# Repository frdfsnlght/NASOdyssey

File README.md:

# NASOdyssey
3D printed NAS based on the Odyssey X86J4125864

[Documentaion](https://frdfsnlght.github.io/NASOdyssey/)

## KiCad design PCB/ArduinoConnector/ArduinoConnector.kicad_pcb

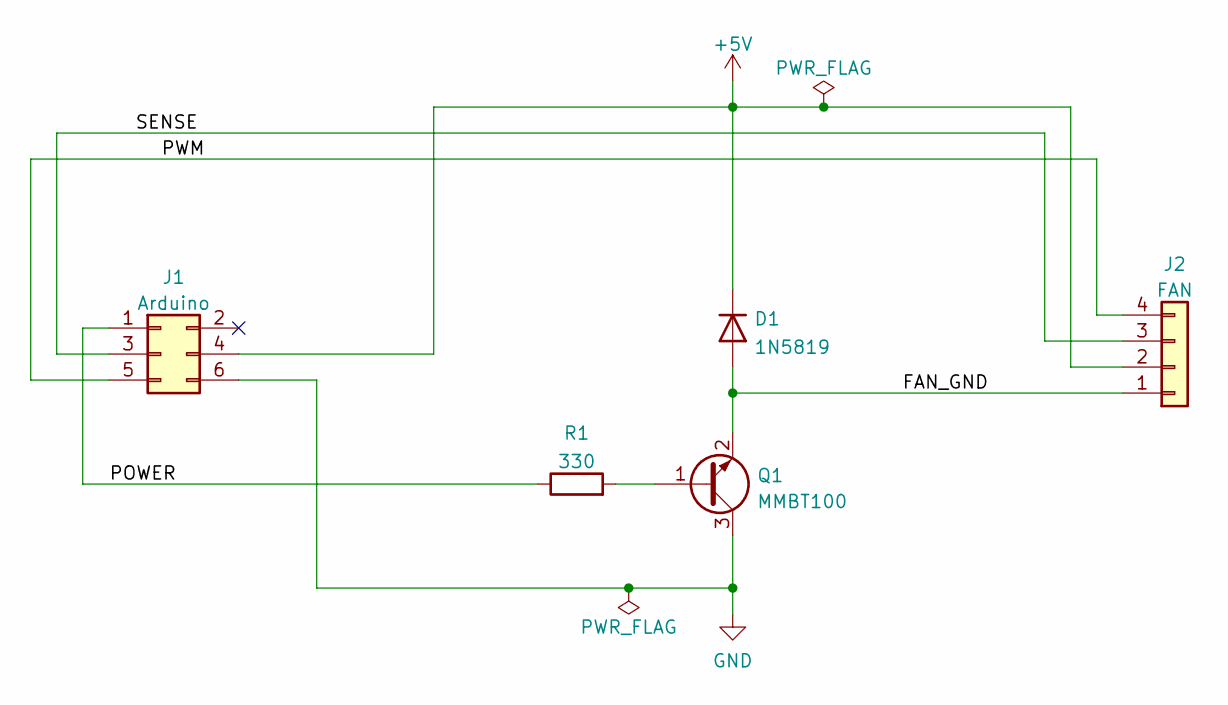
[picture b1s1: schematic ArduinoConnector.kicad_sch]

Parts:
D1: 1N5819; D_SMA
J1: Arduino; PinHeader_2x03_P2.54mm_Vertical
J2: FAN; Molex_KK-254_AE-6410-04A_1x04_P2.54mm_Vertical
Q1: MMBT100; SOT-23
R1: 330; R_0805_2012Metric

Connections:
+5V: D1.1 (K), J1.4, J2.2
/FAN_GND: D1.2 (A), J2.1, Q1.2 (E)
/POWER: J1.1, R1.1
/PWM: J1.5, J2.4
/SENSE: J1.3, J2.3
GND: J1.6, Q1.3 (C)
unnamed: Q1.1 (B), R1.2

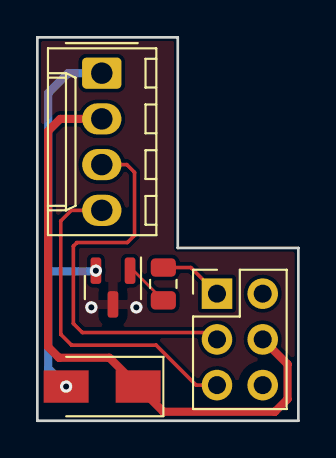
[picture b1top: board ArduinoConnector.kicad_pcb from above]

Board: 2 copper layers, 14.5 x 21.3 mm, 5 parts (0 on the bottom side), 7 nets.

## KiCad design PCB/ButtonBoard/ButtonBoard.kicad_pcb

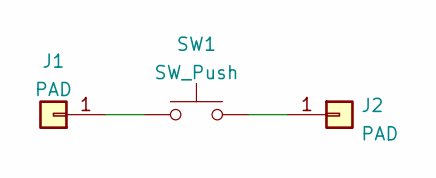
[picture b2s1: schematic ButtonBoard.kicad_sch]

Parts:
J1, J2: PAD; Pin_D1.3mm_L11.0mm
SW1: SW_Push; SW_Push_1P1T_NO_6x6mm_H9.5mm

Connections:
unnamed: J1.1, SW1.1
unnamed: J2.1, SW1.2

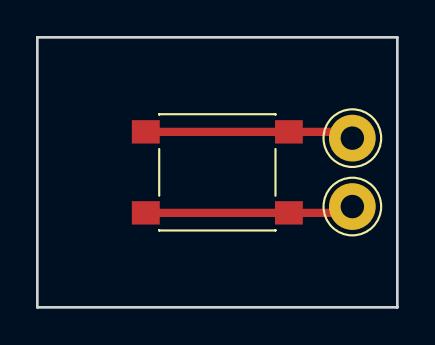
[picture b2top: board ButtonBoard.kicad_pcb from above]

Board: 2 copper layers, 20.0 x 15.0 mm, 3 parts (0 on the bottom side), 2 nets.

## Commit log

2022-03-11 Added do-nothing scritp for container debugging
2022-03-11 Initial PCB circuit
2022-03-11 Added gitignore
2022-03-12 Changes to make it work
2022-03-12 New PCBs
2022-03-13 Fixed background painting
2022-03-13 Generated gerbers
2022-03-13 Switched tx/rx position
2022-03-14 Beginning case design
2022-03-15 More work done
2022-03-16 More work
2022-03-16 Changed pin assignments and redid the PCB
2022-03-17 Trying to fix fan RPM sensing
2022-03-17 Fucking around with the PCB layout
2022-03-17 Fixed RPM detection
2022-03-17 Updated ArduinoFan README
2022-03-17 New version of the ArduinoConnector
2022-03-18 Added gcode files
2022-03-18 Added PrusaSlicer files
2022-03-20 Fixed coloring and added noAddressColor
2022-03-21 Set theme jekyll-theme-cayman
2022-03-21 Added documentation link
2022-03-21 Fixed name
2022-03-21 Lots more content
2022-03-21 More edits
2022-03-22 Tweaked printing info
2022-03-22 Final designs pending any tweaks
2022-03-23 Changing styles and adding carousel
2022-03-24 Changed
2022-03-24 Design finalized
2022-03-26 Adding pictures
2022-03-26 Adding lightbox
2022-03-26 Trying something
2022-03-26 Trying...
2022-03-26 More images
2022-03-26 More pictures
2022-03-27 Tweaked
2022-03-27 Changed form of command
2022-03-27 Added last pics
2022-03-27 Formatting
2022-03-27 Deck now handles hidden cards
2022-03-27 Added wait screen
2022-03-29 Prevent screen from clearing on shutdown
2022-03-29 Changed FS to monitor for usage
2022-04-07 Changed fan curve, FS path
